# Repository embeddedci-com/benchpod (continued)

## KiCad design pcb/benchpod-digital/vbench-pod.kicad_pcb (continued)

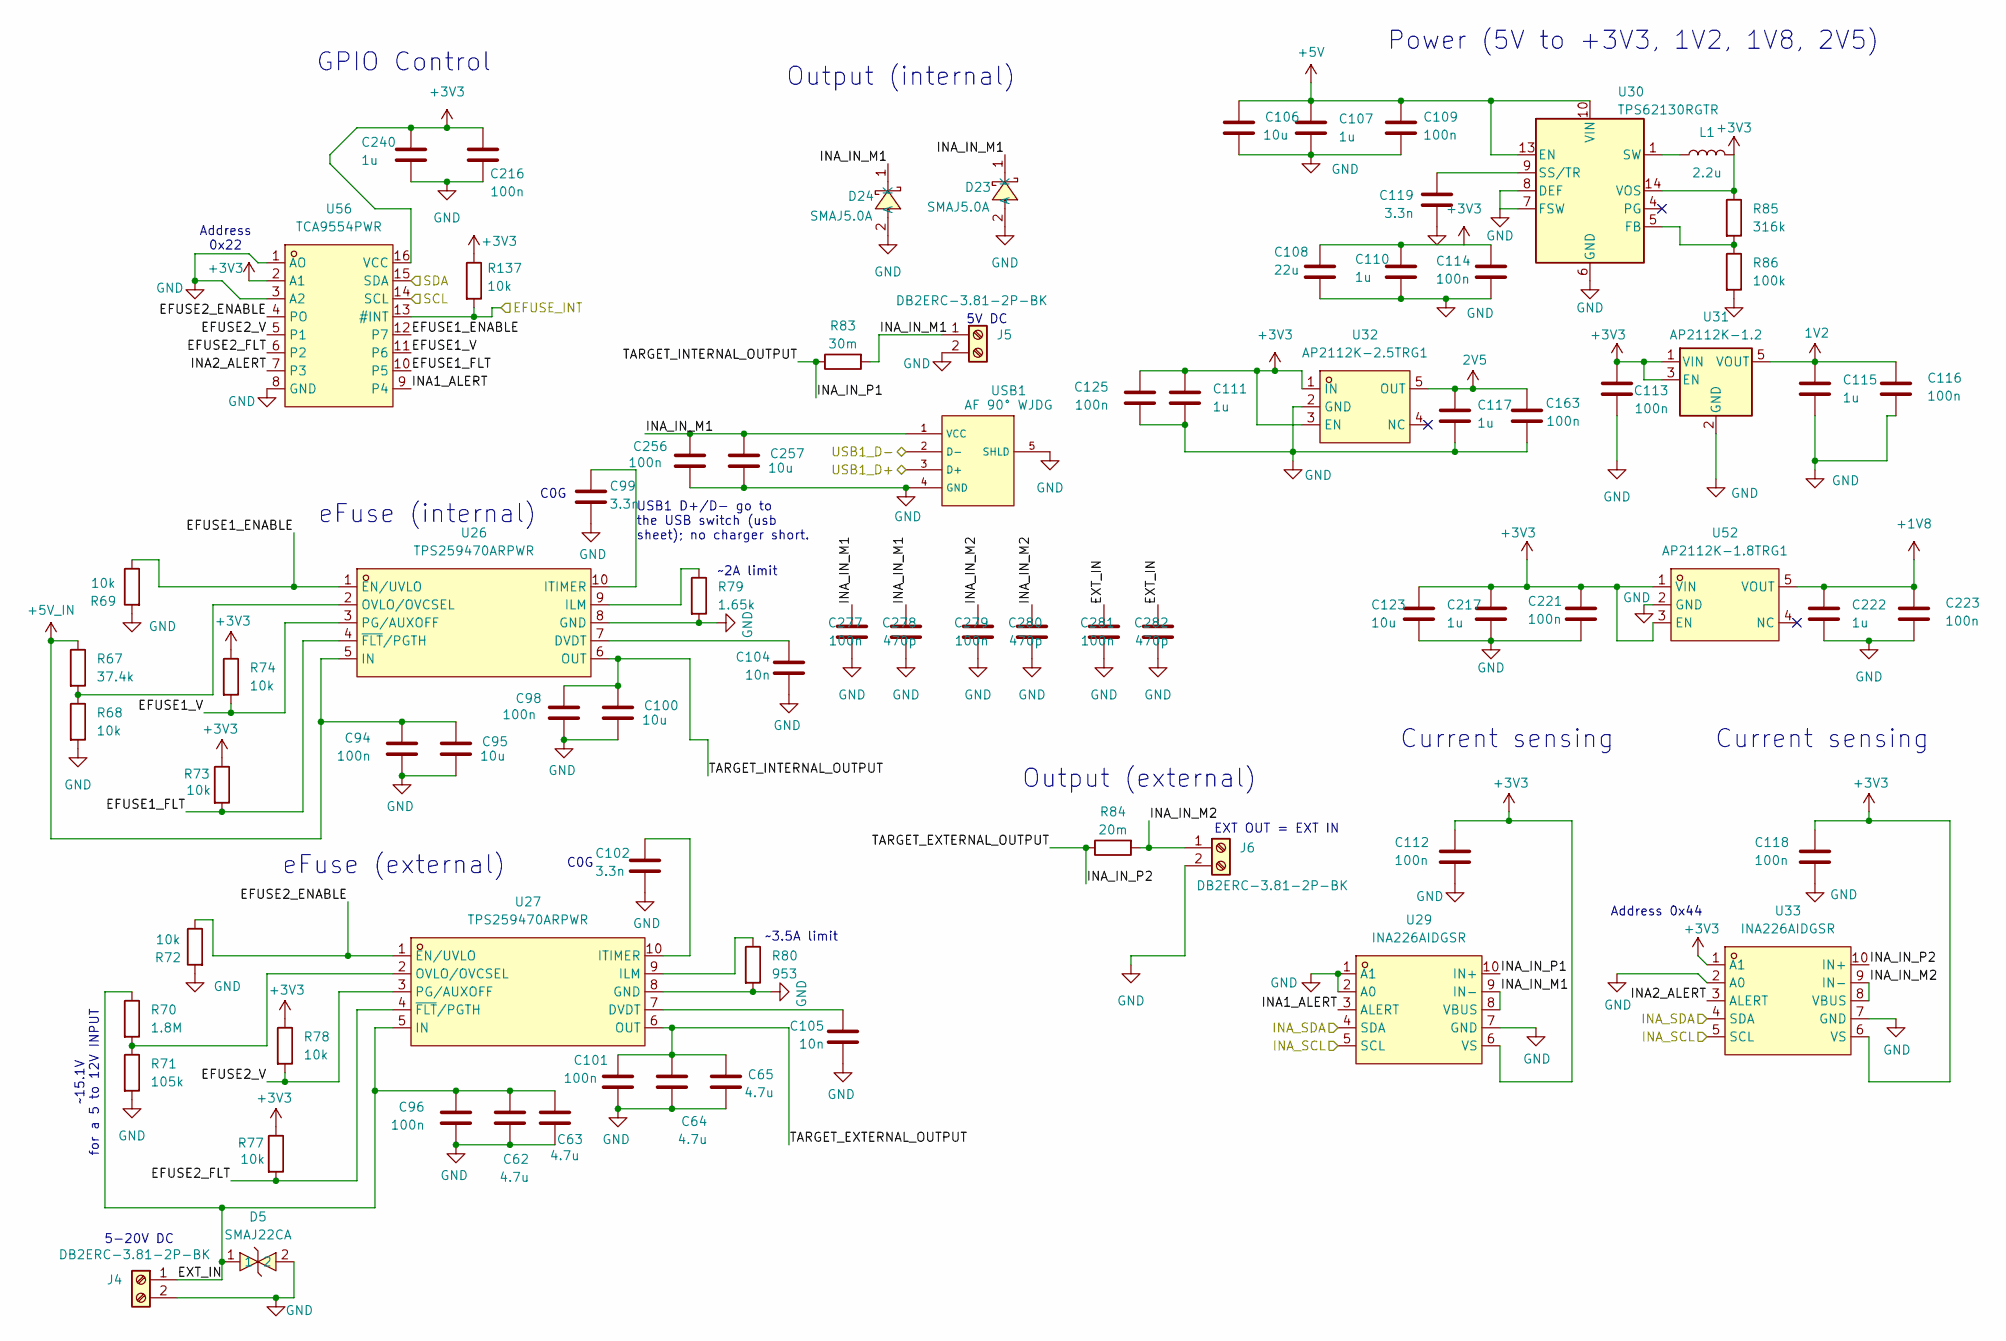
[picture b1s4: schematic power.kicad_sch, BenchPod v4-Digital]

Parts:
C62, C63, C64, C65: 4.7u; C_0805_2012Metric; LCSC C98192
C94, C96, C98, C101, C109, C112, C113, C114, C116, C118, C125, C163, C221, C223, C256, C277, C279, C281: 100n; C_0402_1005Metric; MPN CC0603KRX7R9BB104; LCSC C307331
C95, C100, C106, C257: 10u; C_0603_1608Metric; LCSC C96446
C99, C102, C119: 3.3n; C_0402_1005Metric; LCSC C26404
C104, C105: 10n; C_0402_1005Metric; LCSC C15195
C107, C110, C111, C115, C117, C217, C240: 1u; C_0402_1005Metric; MPN CL05A105KA5NQNC; LCSC C52923
C108: 22u; C_0805_2012Metric; MPN CL21B105KBFNNNE; LCSC C45783
C123: 10u; C_0603_1608Metric; MPN GRM21BR61H106KE43L; LCSC C96446
C216: 100n; C_0402_1005Metric; LCSC C307331
C222: 1u; C_0402_1005Metric; MPN GRM155R61H105KE05D; LCSC C1518208
C278, C280, C282: 470p; C_0402_1005Metric; MPN CC0603KRX7R9BB104; LCSC C1537
D5: SMAJ22CA; C41376408_SMA_L4_3-W2_6-LS5_2-RD; MPN SMAJ22CA; LCSC C5353129
D23, D24: SMAJ5.0A; SMA_L4.3-W2.6-LS5.0-RD; MPN SMAJ5.0A; LCSC Part C2925443
J4, J5, J6: DB2ERC-3.81-2P-BK; C5259145_CONN-TH_2P-P3.81_DB2ERC-3.81-2P-BK; MFR. Part # DB2ERC-3.81-2P-BK; LCSC Part # C5259145
L1: 2.2u; C167869_IND-SMD_L4.0-W4.0_FNR40XXS; LCSC C167869
R67: 37.4k; R_0402_1005Metric; LCSC C185422
R68, R69, R72, R73, R74, R77, R78, R137: 10k; R_0402_1005Metric; LCSC C25744
R70: 1.8M; R_0402_1005Metric; LCSC C38587
R71: 105k; R_0402_1005Metric; LCSC C25742
R79: 1.65k; R_0402_1005Metric; LCSC C25869
R80: 953; R_0402_1005Metric; LCSC C113475
R83: 30m; R_2512_6332Metric; LCSC C2941066
R84: 20m; R_2512_6332Metric; LCSC C915979
R85: 316k; R_0402_1005Metric; LCSC C25777
R86: 100k; R_0402_1005Metric; LCSC C25741
U26, U27: TPS259470ARPWR; VQFN-10_L2.0-W2.0-P0.45-TL; MPN TPS259470ARPWR; LCSC Part C3662799
U29, U33: INA226AIDGSR; VSSOP-10_L3.0-W3.0-P0.50-LS4.9-BL; LCSC Part C49851
U30: TPS62130RGTR; C337502_VQFN-16_L3_0-W3_0-P0_50-BL-EP1_7; LCSC C43590
U31: AP2112K-1.2; SOT-25_L3.0-W1.6-P0.95-LS2.8-BR; LCSC C460310
U32: AP2112K-2.5TRG1; SOT-25-5; MPN AP2112K-2.5TRG1; LCSC Part C176945
U52: AP2112K-1.8TRG1; SOT-25_L3.0-W1.6-P0.95-LS2.8-BL; MPN AP2112K-1.8TRG1; LCSC Part C176944
U56: TCA9554PWR; TSSOP-16_L5.0-W4.4-P0.65-LS6.4-TL; MPN TCA9554PWR; LCSC Part C477924
USB1: AF 90° WJDG; C456018_USB-A-TH_AF-WJDG; LCSC C456018

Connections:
1V2: C115.2, C116.2, U31.5 (VOUT); also elsewhere on the board
2V5: C117.2, C163.2, U32.5 (OUT); also elsewhere on the board
+1V8: C222.2, C223.2, U52.5 (VOUT); also elsewhere on the board
+3V3: C108.2, C110.2, C111.2, C112.2, C113.2, C114.2, C118.2, C123.2, C125.2, C216.1, C217.2, C221.2, C240.2, L1.2, R73.1, R74.1, R77.1, R78.1, R85.1, R137.1, U29.6 (VS), U30.14 (VOS), U31.1 (VIN), U31.3 (EN), U32.1 (IN), U32.3 (EN), U33.1 (A1), U33.6 (VS), U52.1 (VIN), U52.3 (EN), U56.2 (A1), U56.16 (VCC); also elsewhere on the board
+5V: C106.2, C107.2, C109.2, U30.10 (VIN), U30.11 (VIN), U30.12 (VIN), U30.13 (EN); also elsewhere on the board
+5V_IN: C94.2, C95.1, R67.1, U26.5 (IN); also elsewhere on the board
/EFUSE_INT: R137.2, U56.13 (#INT); also elsewhere on the board
/I2C0_SCL: U29.5 (SCL), U33.5 (SCL), U56.14 (SCL); also elsewhere on the board
/I2C0_SDA: U29.4 (SDA), U33.4 (SDA), U56.15 (SDA); also elsewhere on the board
/Power/EFUSE1_ENABLE: R69.1, U26.1 (EN/UVLO), U56.12 (P7)
/Power/EFUSE1_FLT: R73.2, U26.4 (~FLT/PGTH), U56.10 (P5)
/Power/EFUSE1_V: R74.2, U26.3 (PG/AUXOFF), U56.11 (P6)
/Power/EFUSE2_ENABLE: R72.1, U27.1 (EN/UVLO), U56.4 (PO)
/Power/EFUSE2_FLT: R77.2, U27.4 (~FLT/PGTH), U56.6 (P2)
/Power/EFUSE2_V: R78.2, U27.3 (PG/AUXOFF), U56.5 (P1)
/Power/EXT_IN: C62.1, C63.1, C96.2, C281.1, C282.1, D5.1, J4.1, R70.1, U27.5 (IN)
/Power/INA1_ALERT: U29.3 (ALERT), U56.9 (P4)
/Power/INA2_ALERT: U33.3 (ALERT), U56.7 (P3)
/Power/INA_IN_M1: C256.2, C257.1, C277.1, C278.1, D23.1 (K), D24.1 (K), J5.1, R83.2, U29.8 (VBUS), U29.9 (IN-), USB1.1 (VCC)
/Power/INA_IN_M2: C279.1, C280.1, J6.1, R84.2, U33.8 (VBUS), U33.9 (IN-)
/Power/INA_IN_P1: C98.2, C100.1, R83.1, U26.6 (OUT), U29.10 (IN+)
/Power/INA_IN_P2: C64.1, C65.1, C101.2, R84.1, U27.6 (OUT), U33.10 (IN+)
/USB1_D+: USB1.3 (D+); also elsewhere on the board
/USB1_D-: USB1.2 (D-); also elsewhere on the board
GND: C62.2, C63.2, C64.2, C65.2, C94.1, C95.2, C96.1, C98.1, C99.2, C100.2, C101.1, C102.2, C104.2, C105.2, C106.1, C107.1, C108.1, C109.1, C110.1, C111.1, C112.1, C113.1, C114.1, C115.1, C116.1, C117.1, C118.1, C119.2, C123.1, C125.1, C163.1, C216.2, C217.1, C221.1, C222.1, C223.1, C240.1, C256.1, C257.2, C277.2, C278.2, C279.2, C280.2, C281.2, C282.2, D5.2, D23.2 (A), D24.2 (A), J4.2, J5.2, J6.2, R68.2, R69.2, R71.2, R72.2, R79.2, R80.2, R86.2, U26.8 (GND), U27.8 (GND), U29.1 (A1), U29.2 (A0), U29.7 (GND), U30.6 (GND), U30.7 (FSW), U30.8 (DEF), U30.15 (GND), U30.16 (GND), U30.17 (GND), U31.2 (GND), U32.2 (GND), U33.2 (A0), U33.7 (GND), U52.2 (GND), U56.1 (AO), U56.3 (A2), U56.8 (GND), USB1.4 (GND), USB1.5 (SHLD); also elsewhere on the board
unnamed: L1.1, U30.1 (SW), U30.2 (SW), U30.3 (SW)
unnamed: C104.1, U26.7 (DVDT)
unnamed: R79.1, U26.9 (ILM)
unnamed: C99.1, U26.10 (ITIMER)
unnamed: R67.2, R68.1, U26.2 (OVLO/OVCSEL)
unnamed: C105.1, U27.7 (DVDT)
unnamed: R80.1, U27.9 (ILM)
unnamed: C102.1, U27.10 (ITIMER)
unnamed: R70.2, R71.1, U27.2 (OVLO/OVCSEL)
unnamed: R85.2, R86.1, U30.5 (FB)
unnamed: C119.1, U30.9 (SS/TR)

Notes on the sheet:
GPIO Control
USB1 D+/D- go to the USB switch (usb sheet); no charger short.
C0G
Output (internal)
~3.5A limit
eFuse (external)
Current sensing
5-20V DC
5V DC
~2A limit
EXT OUT = EXT IN
Address 0x44
Power (5V to +3V3, 1V2, 1V8, 2V5)
Output (external)
~15.1V for a 5 to 12V INPUT
Address 0x22
eFuse (internal)

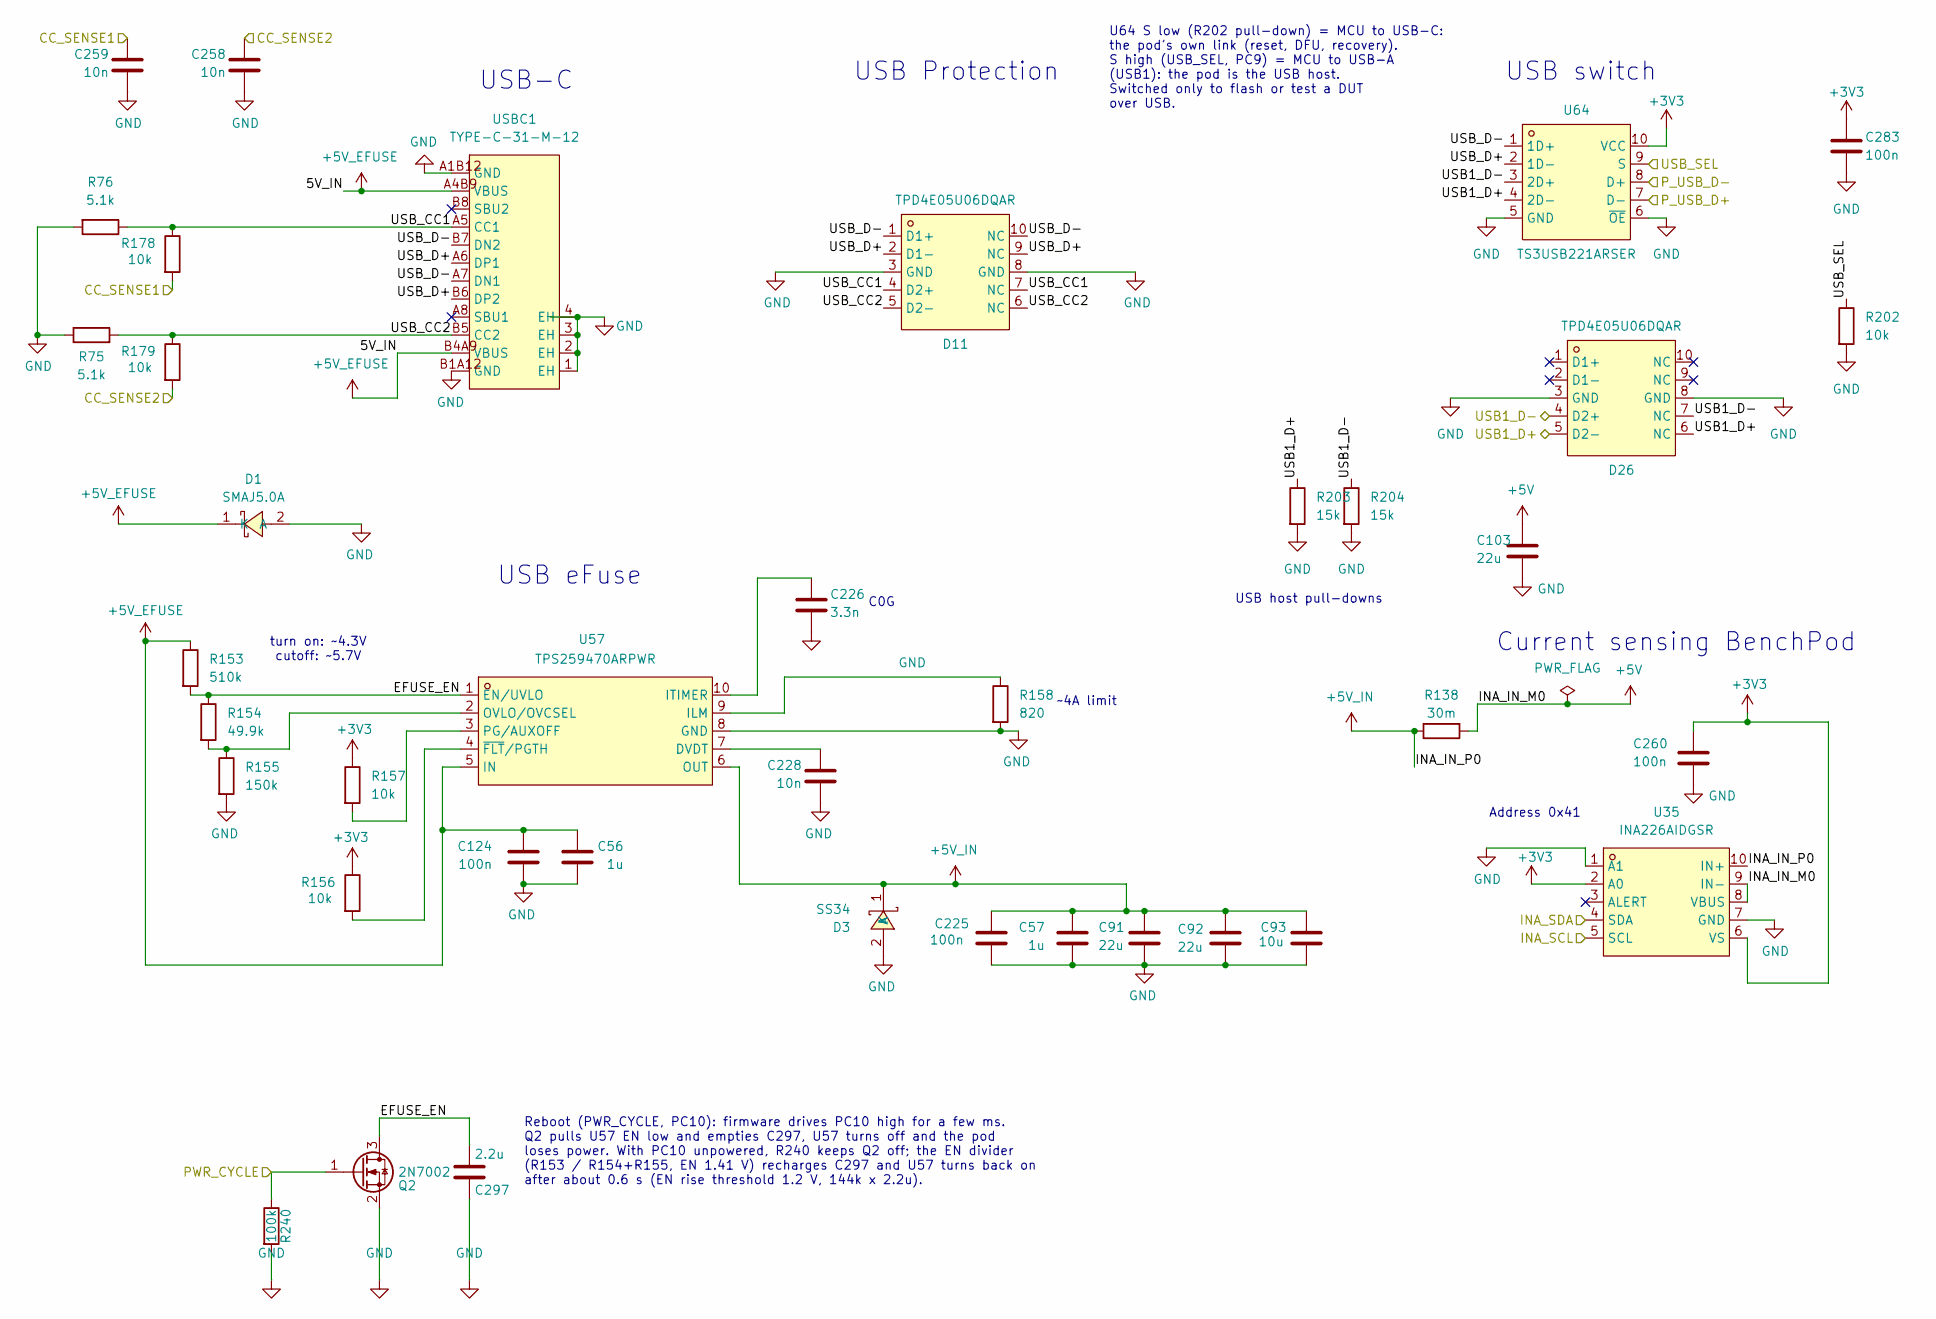
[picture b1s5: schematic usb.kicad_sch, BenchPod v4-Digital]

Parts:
C56: 1u; C_0402_1005Metric; MPN GRM155R61H105KE05D; LCSC C1518208
C57: 1u; C_0402_1005Metric; MPN CL05A105KA5NQNC; LCSC C52923
C91, C92, C103: 22u; C_0805_2012Metric; LCSC C45783
C93: 10u; C_0603_1608Metric; LCSC C96446
C124, C225, C260: 100n; C_0402_1005Metric; MPN CC0603KRX7R9BB104; LCSC C307331
C226: 3.3n; C_0402_1005Metric; LCSC C26404
C228, C258, C259: 10n; C_0402_1005Metric; LCSC C15195
C283: 100n; C_0402_1005Metric; LCSC C307331
C297: 2.2u; C_0603_1608Metric; LCSC C23630
D1: SMAJ5.0A; SMA_L4.3-W2.6-LS5.0-RD; MPN SMAJ5.0A; LCSC Part C2925443
D3: SS34; SMA_L4.3-W2.6-LS5.2-RD; MPN SS34; LCSC Part C3014011
D11, D26: TPD4E05U06DQAR; C138714_USON-10_L2.5-W1.0-P0.50-BL; LCSC C138714
Q2: 2N7002; SOT-23; LCSC C8545
R75, R76: 5.1k; R_0402_1005Metric; LCSC C25905
R138: 30m; R_2512_6332Metric; LCSC C2941066
R153: 510k; R_0603_1608Metric; LCSC C23192
R154: 49.9k; R_0603_1608Metric; LCSC C23184
R155: 150k; R_0603_1608Metric; LCSC C22807
R156, R157, R178, R179, R202: 10k; R_0402_1005Metric; LCSC C25744
R158: 820; R_0603_1608Metric; LCSC C23253
R203, R204: 15k; R_0402_1005Metric; LCSC C25756
R240: 100k; R_0603_1608Metric; LCSC C25803
U35: INA226AIDGSR; VSSOP-10_L3.0-W3.0-P0.50-LS4.9-BL; LCSC Part C49851
U57: TPS259470ARPWR; VQFN-10_L2.0-W2.0-P0.45-TL; MPN TPS259470ARPWR; LCSC Part C3662799
U64: TS3USB221ARSER; C128396_UQFN-10_L2.0-W1.5-P0.50-BL; MPN TS3USB221ARSER; LCSC C128396
USBC1: TYPE-C-31-M-12; USB-C_SMD-TYPE-C-31-M-12_1; MPN TYPE-C-31-M-12; LCSC Part C165948

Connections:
+3V3: C260.2, C283.1, R156.1, R157.1, U35.2 (A0), U35.6 (VS), U64.10 (VCC); also elsewhere on the board
+5V: C103.1, R138.2, U35.8 (VBUS), U35.9 (IN-); also elsewhere on the board
+5V_EFUSE: C56.2, C124.2, D1.1 (K), R153.1, U57.5 (IN), USBC1.A4B9 (VBUS), USBC1.B4A9 (VBUS); also elsewhere on the board
+5V_IN: C57.2, C91.1, C92.1, C93.1, C225.2, D3.1 (K), R138.1, U35.10 (IN+), U57.6 (OUT); also elsewhere on the board
/CC_SENSE1: C259.1, R178.2; also elsewhere on the board
/CC_SENSE2: C258.1, R179.2; also elsewhere on the board
/I2C0_SCL: U35.5 (SCL); also elsewhere on the board
/I2C0_SDA: U35.4 (SDA); also elsewhere on the board
/PWR_CYCLE: Q2.1 (G), R240.1; also elsewhere on the board
/P_USB_D+: U64.7 (D-); also elsewhere on the board
/P_USB_D-: U64.8 (D+); also elsewhere on the board
/USB1_D+: D26.5 (D2-), D26.6 (NC), R203.1, U64.4 (2D-); also elsewhere on the board
/USB1_D-: D26.4 (D2+), D26.7 (NC), R204.1, U64.3 (2D+); also elsewhere on the board
/USB/EFUSE_EN: C297.1, Q2.3 (D), R153.2, R154.1, U57.1 (EN/UVLO)
/USB/USB_CC1: D11.4 (D2+), D11.7 (NC), R76.1, R178.1, USBC1.A5 (CC1)
/USB/USB_CC2: D11.5 (D2-), D11.6 (NC), R75.2, R179.1, USBC1.B5 (CC2)
/USB/USB_D+: D11.2 (D1-), D11.9 (NC), U64.2 (1D-), USBC1.A6 (DP1), USBC1.B6 (DP2)
/USB/USB_D-: D11.1 (D1+), D11.10 (NC), U64.1 (1D+), USBC1.A7 (DN1), USBC1.B7 (DN2)
/USB_SEL: R202.1, U64.9 (S); also elsewhere on the board
GND: C56.1, C57.1, C91.2, C92.2, C93.2, C103.2, C124.1, C225.1, C226.2, C228.2, C258.2, C259.2, C260.1, C283.2, C297.2, D1.2 (A), D3.2 (A), D11.3 (GND), D11.8 (GND), D26.3 (GND), D26.8 (GND), Q2.2 (S), R75.1, R76.2, R155.2, R158.2, R202.2, R203.2, R204.2, R240.2, U35.1 (A1), U35.7 (GND), U57.8 (GND), U64.5 (GND), U64.6 (~OE), USBC1.1 (EH), USBC1.2 (EH), USBC1.3 (EH), USBC1.4 (EH), USBC1.A1B12 (GND), USBC1.B1A12 (GND); also elsewhere on the board
unnamed: C228.1, U57.7 (DVDT)
unnamed: R158.1, U57.9 (ILM)
unnamed: C226.1, U57.10 (ITIMER)
unnamed: R154.2, R155.1, U57.2 (OVLO/OVCSEL)
unnamed: R157.2, U57.3 (PG/AUXOFF)
unnamed: R156.2, U57.4 (~FLT/PGTH)

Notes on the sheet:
USB-C
Current sensing BenchPod
U64 S low (R202 pull-down) = MCU to USB-C: the pod's own link (reset, DFU, recovery). S high (USB_SEL, PC9) = MCU to USB-A (USB1): the pod is the USB host. Switched only to flash or test a DUT over USB.
USB Protection
~4A limit
C0G
turn on: ~4.3V cutoff: ~5.7V
USB switch
USB eFuse
Address 0x41
USB host pull-downs
Reboot (PWR_CYCLE, PC10): firmware drives PC10 high for a few ms. Q2 pulls U57 EN low and empties C297, U57 turns off and the pod loses power. With PC10 unpowered, R240 keeps Q2 off; the EN divider (R153 / R154+R155, EN 1.41 V) recharges C297 and U57 turns back on after about 0.6 s (EN rise thresho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

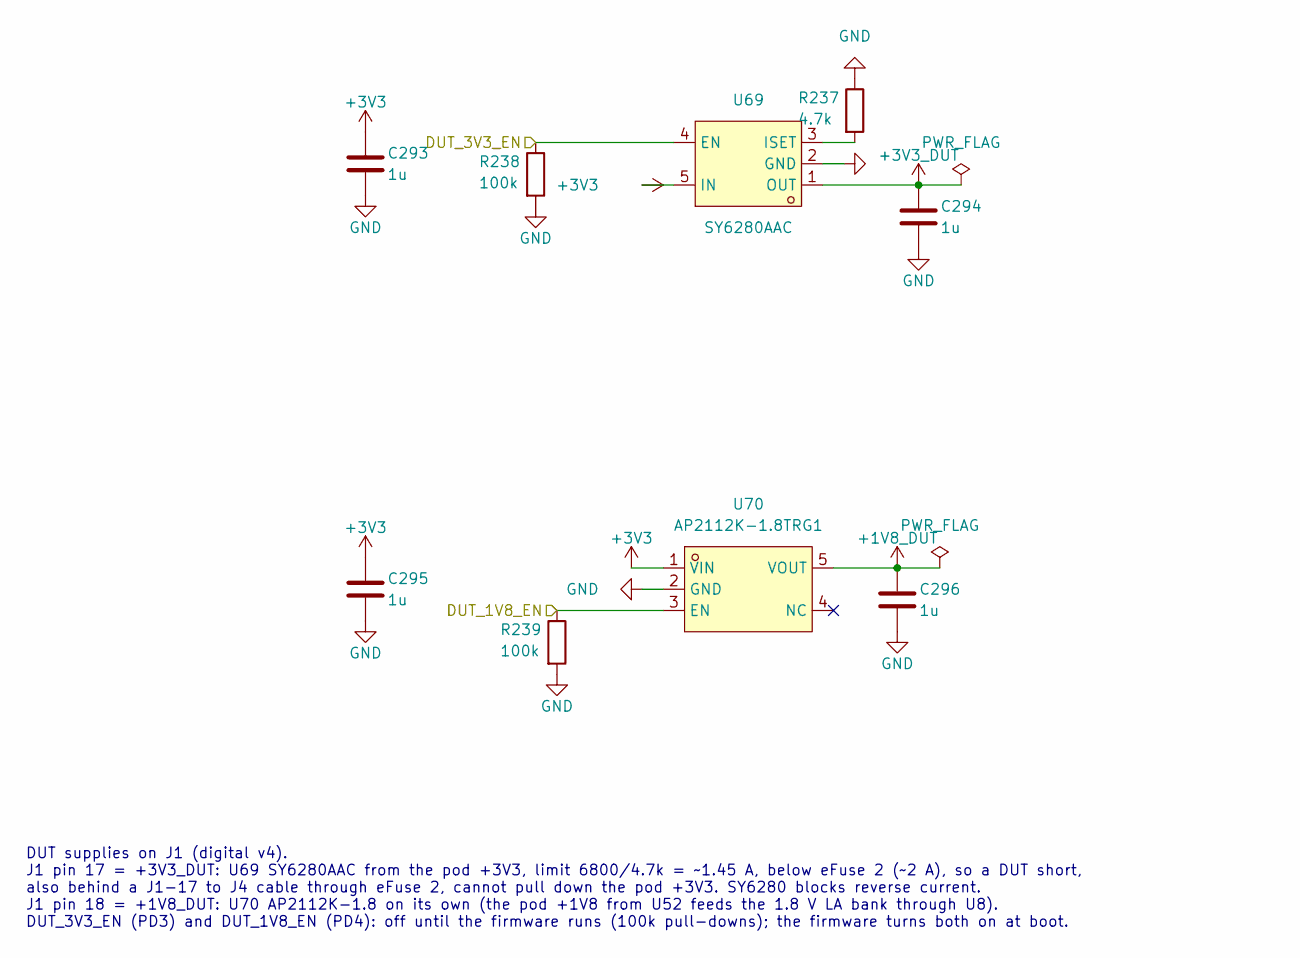
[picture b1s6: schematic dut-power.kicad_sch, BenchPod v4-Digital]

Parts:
C293, C294, C295, C296: 1u; C_0402_1005Metric; MPN CL05A105KA5NQNC; LCSC C52923
R237: 4.7k; R_0402_1005Metric; LCSC C25900
R238, R239: 100k; R_0402_1005Metric; LCSC C25741
U69: SY6280AAC; C55136_SOT-23-5_L3.0-W1.7-P0.95-LS2.8-BL; LCSC C55136
U70: AP2112K-1.8TRG1; SOT-25_L3.0-W1.6-P0.95-LS2.8-BL; MPN AP2112K-1.8TRG1; LCSC Part C176944

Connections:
+3V3: C293.1, C295.1, U69.5 (IN), U70.1 (VIN); also elsewhere on the board
/DUT_1V8_EN: R239.1, U70.3 (EN); also elsewhere on the board
/DUT_3V3_EN: R238.1, U69.4 (EN); also elsewhere on the board
GND: C293.2, C294.2, C295.2, C296.2, R237.1, R238.2, R239.2, U69.2 (GND), U70.2 (GND); also elsewhere on the board
unnamed: R237.2, U69.3 (ISET)

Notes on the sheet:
DUT supplies on J1 (digital v4). J1 pin 17 = +3V3_DUT: U69 SY6280AAC from the pod +3V3, limit 6800/4.7k = ~1.45 A, below eFuse 2 (~2 A), so a DUT short, also behind a J1-17 to J4 cable through eFuse 2, cannot pull down the pod +3V3. SY6280 blocks reverse current. J1 pin 18 = +1V8_DUT: U70 AP2112K-1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

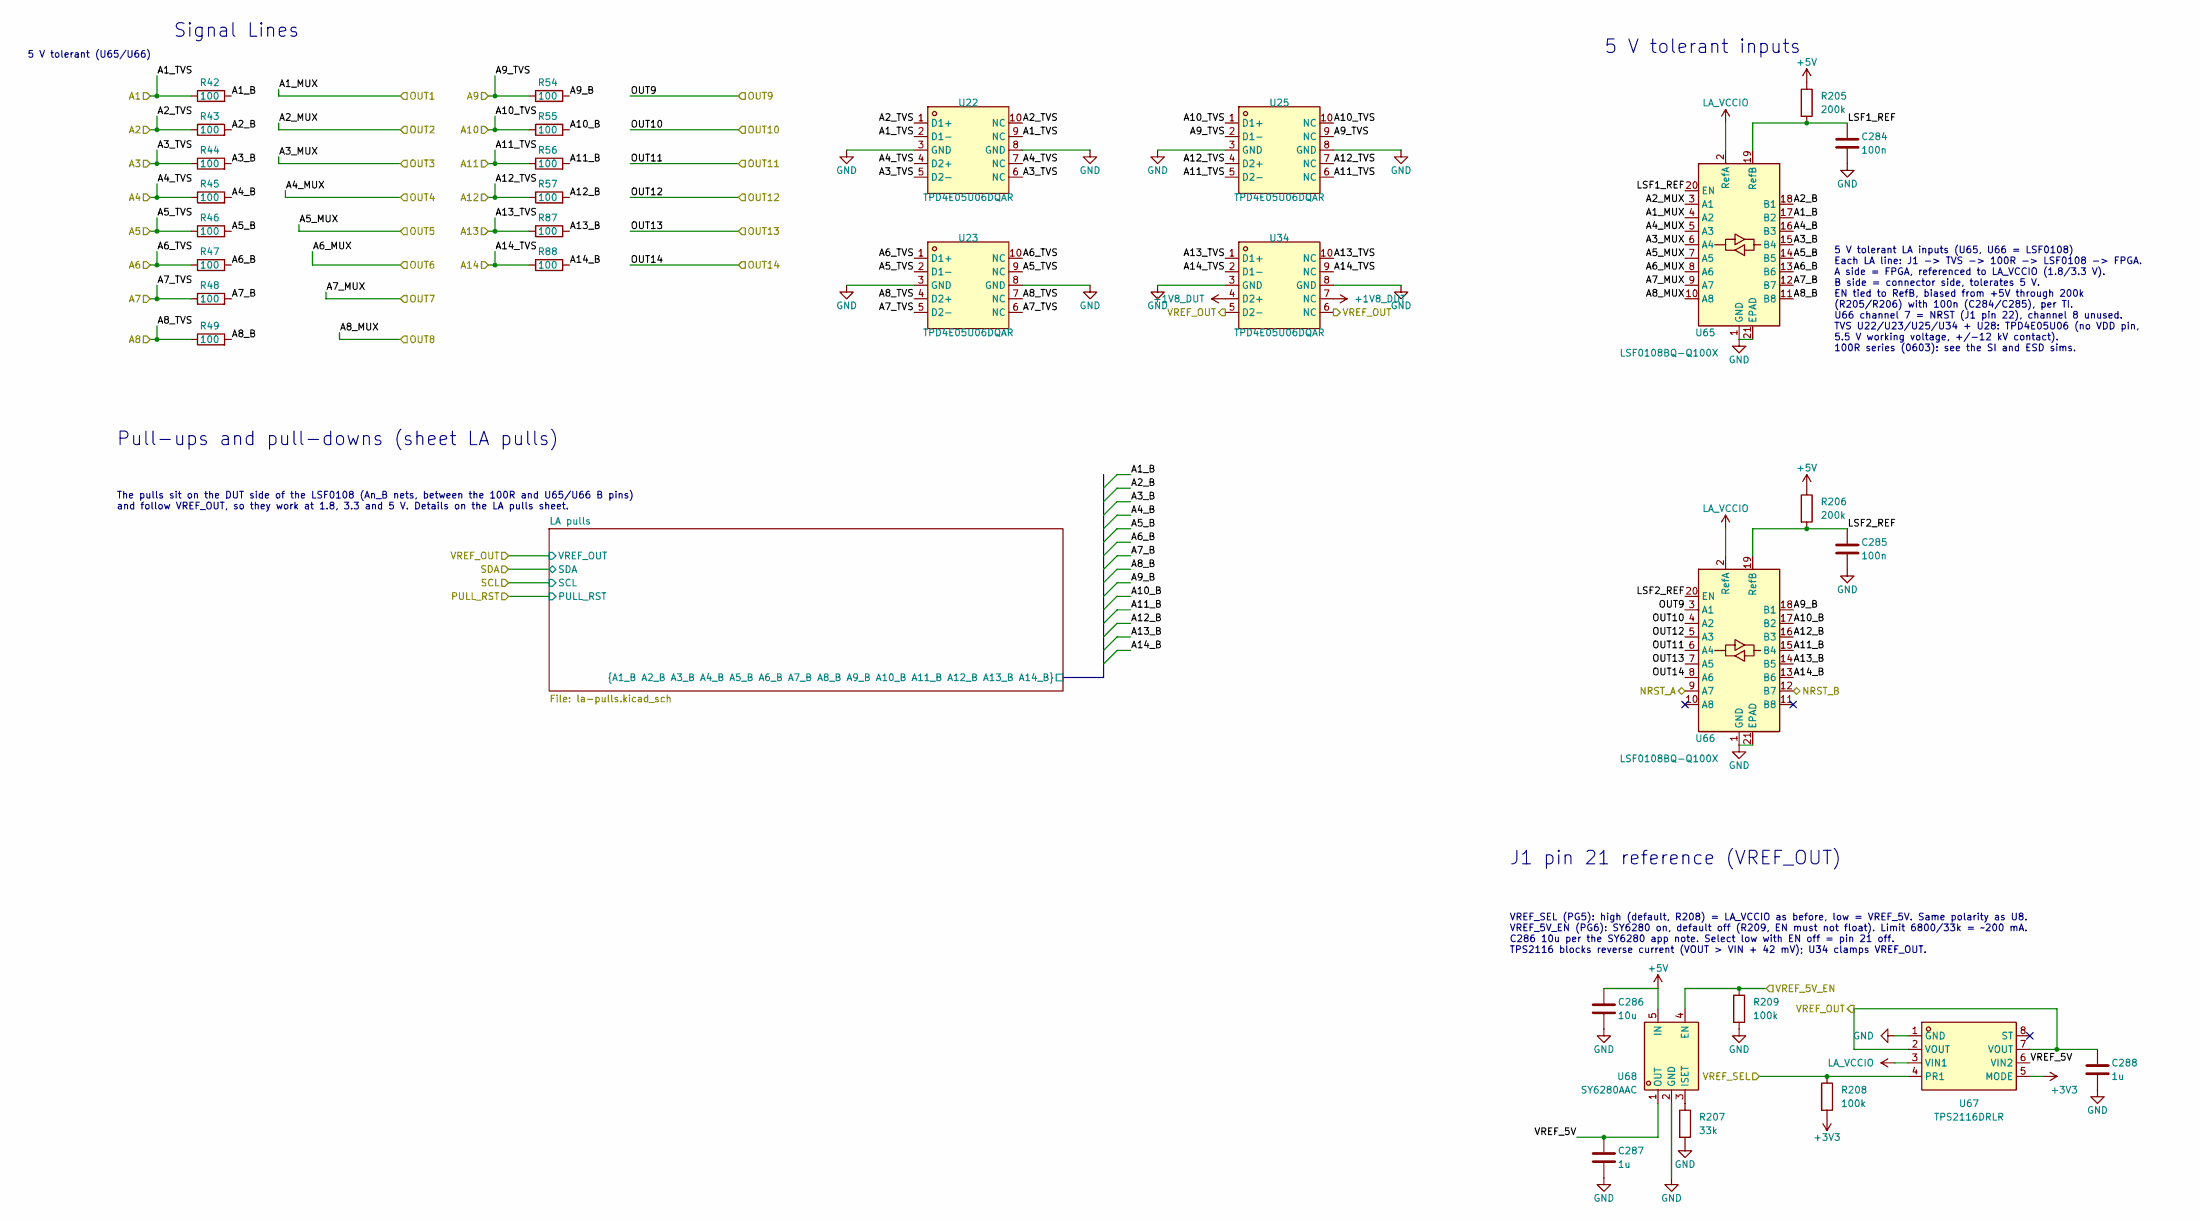
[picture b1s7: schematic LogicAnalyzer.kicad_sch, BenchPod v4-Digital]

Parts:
C284, C285: 100n; C_0402_1005Metric; LCSC C307331
C286: 10u; C_0603_1608Metric; LCSC C96446
C287, C288: 1u; C_0402_1005Metric; LCSC C52923
R42, R43, R44, R45, R46, R47, R48, R49, R54, R55, R56, R57, R87, R88: 100; R_0603_1608Metric; Manufacturer_Part_Number PS03W4F1000T5E; LCSC C2784878
R205, R206: 200k; R_0402_1005Metric; LCSC C25764
R207: 33k; R_0402_1005Metric; LCSC C25779
R208, R209: 100k; R_0402_1005Metric; LCSC C25741
U22, U23, U25, U34: TPD4E05U06DQAR; C138714_USON-10_L2.5-W1.0-P0.50-BL; LCSC C138714
U65, U66: LSF0108BQ-Q100X; DHVQFN-20-1EP_2.5x4.5mm_P0.5mm_EP1x3mm; LCSC C551521
U67: TPS2116DRLR; SOT-583-8_L2.1-W1.6-P0.50-LS1.6-BL; MPN TPS2116DRLR; LCSC Part C3235557
U68: SY6280AAC; C55136_SOT-23-5_L3.0-W1.7-P0.95-LS2.8-BL; LCSC C55136

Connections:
+3V3: R208.2, U67.5 (MODE); also elsewhere on the board
+5V: C286.1, R205.1, R206.1, U68.5 (IN); also elsewhere on the board
/LA_INPUT1: R42.1, U22.2 (D1-), U22.9 (NC); also elsewhere on the board
/LA_INPUT2: R43.1, U22.1 (D1+), U22.10 (NC); also elsewhere on the board
/LA_INPUT3: R44.1, U22.5 (D2-), U22.6 (NC); also elsewhere on the board
/LA_INPUT4: R45.1, U22.4 (D2+), U22.7 (NC); also elsewhere on the board
/LA_INPUT5: R46.1, U23.2 (D1-), U23.9 (NC); also elsewhere on the board
/LA_INPUT6: R47.1, U23.1 (D1+), U23.10 (NC); also elsewhere on the board
/LA_INPUT7: R48.1, U23.5 (D2-), U23.6 (NC); also elsewhere on the board
/LA_INPUT8: R49.1, U23.4 (D2+), U23.7 (NC); also elsewhere on the board
/LA_INPUT9: R54.1, U25.2 (D1-), U25.9 (NC); also elsewhere on the board
/LA_INPUT10: R55.1, U25.1 (D1+), U25.10 (NC); also elsewhere on the board
/LA_INPUT11: R56.1, U25.5 (D2-), U25.6 (NC); also elsewhere on the board
/LA_INPUT12: R57.1, U25.4 (D2+), U25.7 (NC); also elsewhere on the board
/LA_INPUT13: R87.1, U34.1 (D1+), U34.10 (NC); also elsewhere on the board
/LA_INPUT14: R88.1, U34.2 (D1-), U34.9 (NC); also elsewhere on the board
/LA_OUT1: U65.4 (A2); also elsewhere on the board
/LA_OUT2: U65.3 (A1); also elsewhere on the board
/LA_OUT3: U65.6 (A4); also elsewhere on the board
/LA_OUT4: U65.5 (A3); also elsewhere on the board
/LA_OUT5: U65.7 (A5); also elsewhere on the board
/LA_OUT6: U65.8 (A6); also elsewhere on the board
/LA_OUT7: U65.9 (A7); also elsewhere on the board
/LA_OUT8: U65.10 (A8); also elsewhere on the board
/LA_OUT9: U66.3 (A1); also elsewhere on the board
/LA_OUT10: U66.4 (A2); also elsewhere on the board
/LA_OUT11: U66.6 (A4); also elsewhere on the board
/LA_OUT12: U66.5 (A3); also elsewhere on the board
/LA_OUT13: U66.7 (A5); also elsewhere on the board
/LA_OUT14: U66.8 (A6); also elsewhere on the board
/LogicAnalyzer/LA pulls/A1_B: R42.2, U65.17 (B2); also elsewhere on the board
/LogicAnalyzer/LA pulls/A2_B: R43.2, U65.18 (B1); also elsewhere on the board
/LogicAnalyzer/LA pulls/A3_B: R44.2, U65.15 (B4); also elsewhere on the board
/LogicAnalyzer/LA pulls/A4_B: R45.2, U65.16 (B3); also elsewhere on the board
/LogicAnalyzer/LA pulls/A5_B: R46.2, U65.14 (B5); also elsewhere on the board
/LogicAnalyzer/LA pulls/A6_B: R47.2, U65.13 (B6); also elsewhere on the board
/LogicAnalyzer/LA pulls/A7_B: R48.2, U65.12 (B7); also elsewhere on the board
/LogicAnalyzer/LA pulls/A8_B: R49.2, U65.11 (B8); also elsewhere on the board
/LogicAnalyzer/LA pulls/A9_B: R54.2, U66.18 (B1); also elsewhere on the board
/LogicAnalyzer/LA pulls/A10_B: R55.2, U66.17 (B2); also elsewhere on the board
/LogicAnalyzer/LA pulls/A11_B: R56.2, U66.15 (B4); also elsewhere on the board
/LogicAnalyzer/LA pulls/A12_B: R57.2, U66.16 (B3); also elsewhere on the board
/LogicAnalyzer/LA pulls/A13_B: R87.2, U66.14 (B5); also elsewhere on the board
/LogicAnalyzer/LA pulls/A14_B: R88.2, U66.13 (B6); also elsewhere on the board
/LogicAnalyzer/LSF1_REF: C284.1, R205.2, U65.19 (RefB), U65.20 (EN)
/LogicAnalyzer/LSF2_REF: C285.1, R206.2, U66.19 (RefB), U66.20 (EN)
/LogicAnalyzer/VREF_5V: C287.1, U67.6 (VIN2), U68.1 (OUT)
/NRST_A: U66.9 (A7); also elsewhere on the board
/NRST_B: U66.12 (B7); also elsewhere on the board
/VREF_5V_EN: R209.1, U68.4 (EN); also elsewhere on the board
/VREF_OUT: C288.1, U34.5 (D2-), U34.6 (NC), U67.2 (VOUT), U67.7 (VOUT); also elsewhere on the board
/VREF_SEL: R208.1, U67.4 (PR1); also elsewhere on the board
GND: C284.2, C285.2, C286.2, C287.2, C288.2, R207.2, R209.2, U22.3 (GND), U22.8 (GND), U23.3 (GND), U23.8 (GND), U25.3 (GND), U25.8 (GND), U34.3 (GND), U34.8 (GND), U65.1 (GND), U65.21 (EPAD), U66.1 (GND), U66.21 (EPAD), U67.1 (GND), U68.2 (GND); also elsewhere on the board
LA_VCCIO: U65.2 (RefA), U66.2 (RefA), U67.3 (VIN1); also elsewhere on the board
unnamed: R207.1, U68.3 (ISET)

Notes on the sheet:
5 V tolerant LA inputs (U65, U66 = LSF0108) Each LA line: J1 -> TVS -> 100R -> LSF0108 -> FPGA. A side = FPGA, referenced to LA_VCCIO (1.8/3.3 V). B side = connector side, tolerates 5 V. EN tied to RefB, biased from +5V through 200k (R205/R206) with 100n (C284/C285), per TI. U66 channel 7 = NRST (J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
J1 pin 21 reference (VREF_OUT)
5 V tolerant (U65/U66)
Pull-ups and pull-downs (sheet LA pulls)
VREF_SEL (PG5): high (default, R208) = LA_VCCIO as before, low = VREF_5V. Same polarity as U8. VREF_5V_EN (PG6): SY6280 on, default off (R209, EN must not float). Limit 6800/33k = ~200 mA. C286 10u per the SY6280 app note. Select low with EN off = pin 21 off. TPS2116 blocks reverse current (VOUT > 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
5 V tolerant inputs
The pulls sit on the DUT side of the LSF0108 (An_B nets, between the 100R and U65/U66 B pins) and follow VREF_OUT, so they work at 1.8, 3.3 and 5 V. Details on the LA pulls sheet.
Signal Lines

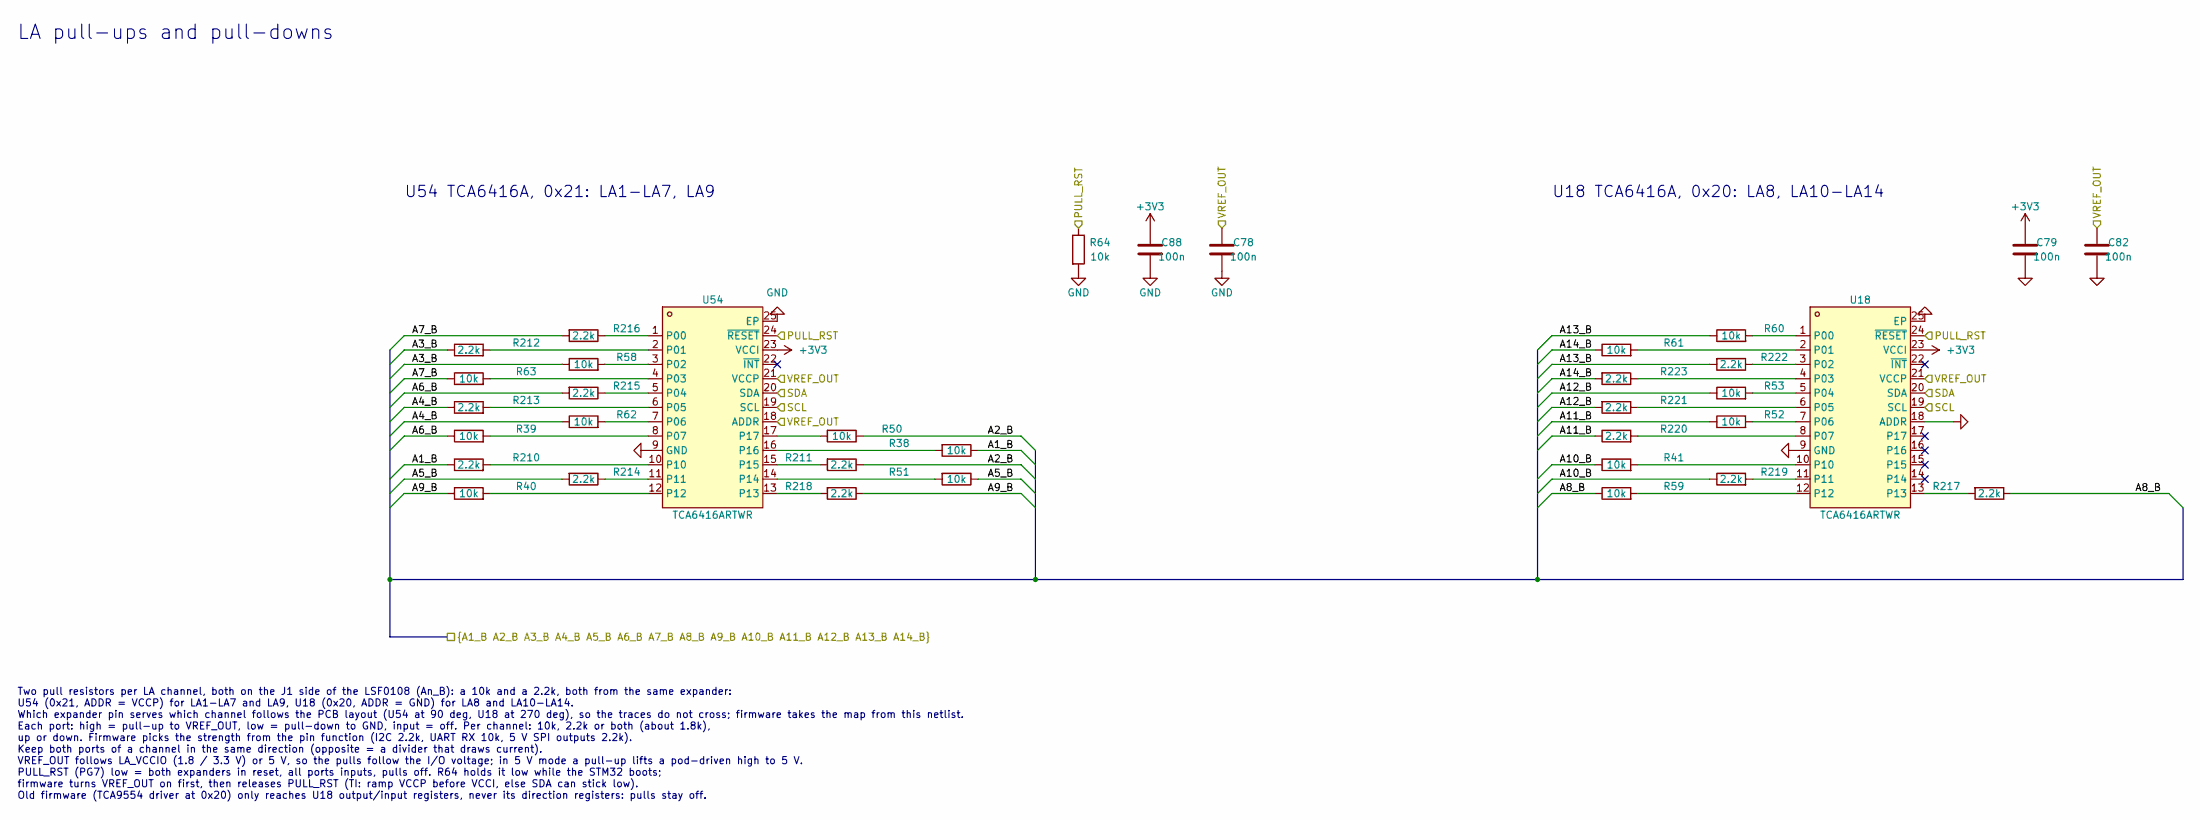
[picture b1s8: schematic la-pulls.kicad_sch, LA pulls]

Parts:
C78, C79, C82, C88: 100n; C_0402_1005Metric; LCSC C307331
R38, R39, R40, R41, R50, R51, R52, R53, R58, R59, R60, R61, R62, R63, R64: 10k; R_0402_1005Metric; LCSC C25744
R210, R211, R212, R213, R214, R215, R216, R217, R218, R219, R220, R221, R222, R223: 2.2k; R_0402_1005Metric; LCSC C25879
U18, U54: TCA6416ARTWR; WQFN-24_L4.0-W4.0-P0.50-TL-EP2.5; MPN TCA6416ARTWR; LCSC C182336

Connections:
+3V3: C79.1, C88.1, U18.23 (VCCI), U54.23 (VCCI); also elsewhere on the board
/I2C0_SCL: U18.19 (SCL), U54.19 (SCL); also elsewhere on the board
/I2C0_SDA: U18.20 (SDA), U54.20 (SDA); also elsewhere on the board
/LogicAnalyzer/LA pulls/A1_B: R38.1, R210.1; also elsewhere on the board
/LogicAnalyzer/LA pulls/A2_B: R50.1, R211.1; also elsewhere on the board
/LogicAnalyzer/LA pulls/A3_B: R58.1, R212.1; also elsewhere on the board
/LogicAnalyzer/LA pulls/A4_B: R62.1, R213.1; also elsewhere on the board
/LogicAnalyzer/LA pulls/A5_B: R51.1, R214.2; also elsewhere on the board
/LogicAnalyzer/LA pulls/A6_B: R39.1, R215.2; also elsewhere on the board
/LogicAnalyzer/LA pulls/A7_B: R63.1, R216.2; also elsewhere on the board
/LogicAnalyzer/LA pulls/A8_B: R59.1, R217.1; also elsewhere on the board
/LogicAnalyzer/LA pulls/A9_B: R40.1, R218.1; also elsewhere on the board
/LogicAnalyzer/LA pulls/A10_B: R41.1, R219.1; also elsewhere on the board
/LogicAnalyzer/LA pulls/A11_B: R52.1, R220.1; also elsewhere on the board
/LogicAnalyzer/LA pulls/A12_B: R53.1, R221.2; also elsewhere on the board
/LogicAnalyzer/LA pulls/A13_B: R60.1, R222.2; also elsewhere on the board
/LogicAnalyzer/LA pulls/A14_B: R61.1, R223.2; also elsewhere on the board
/PULL_RST: R64.1, U18.24 (~RESET), U54.24 (~RESET); also elsewhere on the board
/VREF_OUT: C78.1, C82.1, U18.21 (VCCP), U54.18 (ADDR), U54.21 (VCCP); also elsewhere on the board
GND: C78.2, C79.2, C82.2, C88.2, R64.2, U18.9 (GND), U18.18 (ADDR), U18.25 (EP), U54.9 (GND), U54.25 (EP); also elsewhere on the board
unnamed: R60.2, U18.1 (P00)
unnamed: R61.2, U18.2 (P01)
unnamed: R222.1, U18.3 (P02)
unnamed: R223.1, U18.4 (P03)
unnamed: R53.2, U18.5 (P04)
unnamed: R221.1, U18.6 (P05)
unnamed: R52.2, U18.7 (P06)
unnamed: R220.2, U18.8 (P07)
unnamed: R41.2, U18.10
unnamed: R219.2, U18.11
unnamed: R59.2, U18.12
unnamed: R217.2, U18.13
unnamed: R216.1, U54.1 (P00)
unnamed: R212.2, U54.2 (P01)
unnamed: R58.2, U54.3 (P02)
unnamed: R63.2, U54.4 (P03)
unnamed: R215.1, U54.5 (P04)
unnamed: R213.2, U54.6 (P05)
unnamed: R62.2, U54.7 (P06)
unnamed: R39.2, U54.8 (P07)
unnamed: R210.2, U54.10
unnamed: R214.1, U54.11
unnamed: R40.2, U54.12
unnamed: R218.2, U54.13
unnamed: R51.2, U54.14
unnamed: R211.2, U54.15
unnamed: R38.2, U54.16
unnamed: R50.2, U54.17

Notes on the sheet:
Two pull resistors per LA channel, both on the J1 side of the LSF0108 (An_B): a 10k and a 2.2k, both from the same expander: U54 (0x21, ADDR = VCCP) for LA1-LA7 and LA9, U18 (0x20, ADDR = GND) for LA8 and LA10-LA14. Which expander pin serves which channel follows the PCB layout (U54 at 90 deg, U18 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
U54 TCA6416A, 0x21: LA1-LA7, LA9
U18 TCA6416A, 0x20: LA8, LA10-LA14
LA pull-ups and pull-downs

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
